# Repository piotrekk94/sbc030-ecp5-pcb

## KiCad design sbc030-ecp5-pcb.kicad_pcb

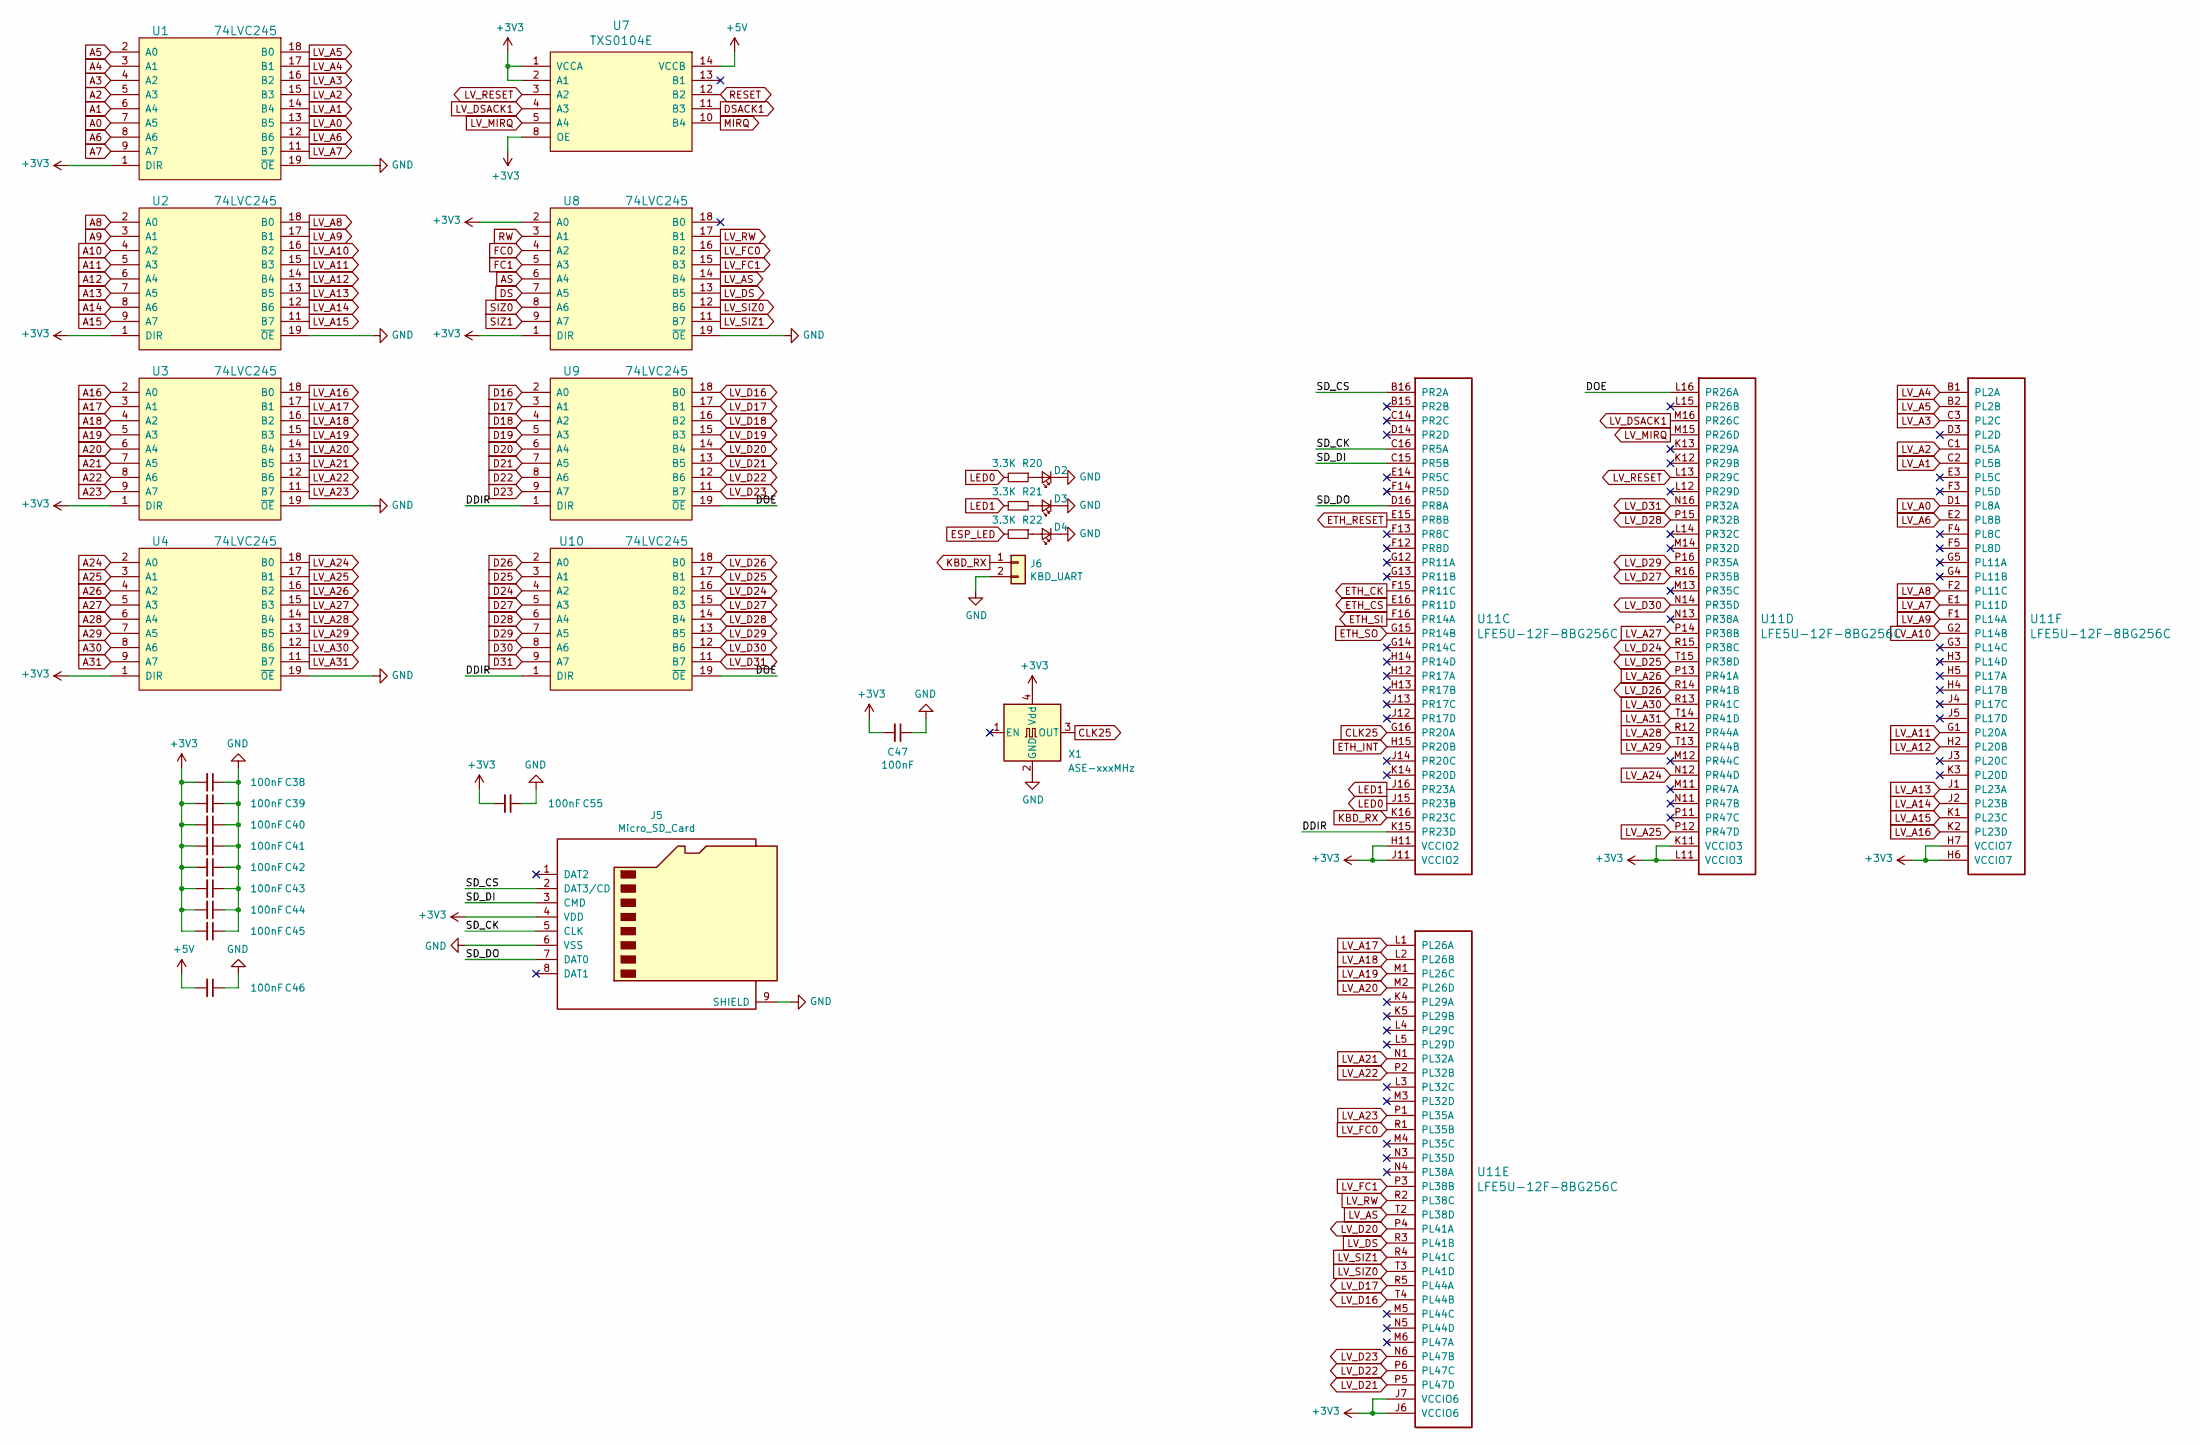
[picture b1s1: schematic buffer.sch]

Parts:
C38, C39, C40, C41, C42, C43, C44, C45, C46, C47, C55: 100nF; C_0603_1608Metric
D2, D3, D4: LED_Small; LED_0603_1608Metric
J5: Micro_SD_Card; microSD_HC_Wuerth_693072010801
J6: KBD_UART; PinHeader_1x02_P2.54mm_Vertical
R20, R21, R22: 3.3K; R_0603_1608Metric
U1, U2, U3, U4, U8, U9, U10: 74LVC245; TSSOP-20_4.4x6.5mm_P0.65mm
U7: TXS0104E; TSSOP-14_4.4x5mm_P0.65mm
U11: LFE5U-12F-8BG256C; BGA-256_14.0x14.0mm_Layout16x16_P0.8mm_Ball0.45mm_Pad0.32mm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
X1: ASE-xxxMHz; Oscillator_SMD_Abracon_ASE-4Pin_3.2x2.5mm

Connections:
+3V3: C38.2, C39.2, C40.2, C41.2, C42.2, C43.2, C44.2, C45.2, C47.2, C55.2, J5.4 (VDD), U1.1 (DIR), U1.20 (VCC), U2.1 (DIR), U2.20 (VCC), U3.1 (DIR), U3.20 (VCC), U4.1 (DIR), U4.20 (VCC), U7.1 (VCCA), U7.2 (A1), U7.8 (OE), U8.1 (DIR), U8.2 (A0), U8.20 (VCC), U9.20 (VCC), U10.20 (VCC), U11.H6 (VCCIO7), U11.H7 (VCCIO7), U11.H11 (VCCIO2), U11.J6 (VCCIO6), U11.J7 (VCCIO6), U11.J11 (VCCIO2), U11.K11 (VCCIO3), U11.L11 (VCCIO3), X1.4 (Vdd); also elsewhere on the board
+5V: C46.2, U7.14 (VCCB); also elsewhere on the board
/IO Buffers/DDIR: U9.1 (DIR), U10.1 (DIR), U11.K15 (PR23D)
/IO Buffers/DOE: U9.19 (~OE), U10.19 (~OE), U11.L16 (PR26A)
/IO Buffers/SD_CK: J5.5 (CLK), U11.C16 (PR5A)
/IO Buffers/SD_CS: J5.2 (DAT3/CD), U11.B16 (PR2A)
/IO Buffers/SD_DI: J5.3 (CMD), U11.C15 (PR5B)
/IO Buffers/SD_DO: J5.7 (DAT0), U11.D16 (PR8A)
A0: U1.7 (A5); also elsewhere on the board
A1: U1.6 (A4); also elsewhere on the board
A2: U1.5 (A3); also elsewhere on the board
A3: U1.4 (A2); also elsewhere on the board
A4: U1.3 (A1); also elsewhere on the board
A5: U1.2 (A0); also elsewhere on the board
A6: U1.8 (A6); also elsewhere on the board
A7: U1.9 (A7); also elsewhere on the board
A8: U2.2 (A0); also elsewhere on the board
A9: U2.3 (A1); also elsewhere on the board
A10: U2.4 (A2); also elsewhere on the board
A11: U2.5 (A3); also elsewhere on the board
A12: U2.6 (A4); also elsewhere on the board
A13: U2.7 (A5); also elsewhere on the board
A14: U2.8 (A6); also elsewhere on the board
A15: U2.9 (A7); also elsewhere on the board
A16: U3.2 (A0); also elsewhere on the board
A17: U3.3 (A1); also elsewhere on the board
A18: U3.4 (A2); also elsewhere on the board
A19: U3.5 (A3); also elsewhere on the board
A20: U3.6 (A4); also elsewhere on the board
A21: U3.7 (A5); also elsewhere on the board
A22: U3.8 (A6); also elsewhere on the board
A23: U3.9 (A7); also elsewhere on the board
A24: U4.2 (A0); also elsewhere on the board
A25: U4.3 (A1); also elsewhere on the board
A26: U4.4 (A2); also elsewhere on the board
A27: U4.5 (A3); also elsewhere on the board
A28: U4.6 (A4); also elsewhere on the board
A29: U4.7 (A5); also elsewhere on the board
A30: U4.8 (A6); also elsewhere on the board
A31: U4.9 (A7); also elsewhere on the board
AS: U8.6 (A4); also elsewhere on the board
CLK25: U11.G16 (PR20A), X1.3 (OUT); also elsewhere on the board
D16: U9.2 (A0); also elsewhere on the board
D17: U9.3 (A1); also elsewhere on the board
D18: U9.4 (A2); also elsewhere on the board
D19: U9.5 (A3); also elsewhere on the board
D20: U9.6 (A4); also elsewhere on the board
D21: U9.7 (A5); also elsewhere on the board
D22: U9.8 (A6); also elsewhere on the board
D23: U9.9 (A7); also elsewhere on the board
D24: U10.4 (A2); also elsewhere on the board
D25: U10.3 (A1); also elsewhere on the board
D26: U10.2 (A0); also elsewhere on the board
D27: U10.5 (A3); also elsewhere on the board
D28: U10.6 (A4); also elsewhere on the board
D29: U10.7 (A5); also elsewhere on the board
D30: U10.8 (A6); also elsewhere on the board
D31: U10.9 (A7); also elsewhere on the board
DS: U8.7 (A5); also elsewhere on the board
DSACK1: U7.11 (B3); also elsewhere on the board
ESP_LED: R22.2; also elsewhere on the board
ETH_CK: U11.F15 (PR11C); also elsewhere on the board
ETH_CS: U11.E16 (PR11D); also elsewhere on the board
ETH_INT: U11.H15 (PR20B); also elsewhere on the board
ETH_RESET: U11.E15 (PR8B); also elsewhere on the board
ETH_SI: U11.F16 (PR14A); also elsewhere on the board
ETH_SO: U11.G15 (PR14B); also elsewhere on the board
FC0: U8.4 (A2); also elsewhere on the board
FC1: U8.5 (A3); also elsewhere on the board
GND: C38.1, C39.1, C40.1, C41.1, C42.1, C43.1, C44.1, C45.1, C46.1, C47.1, C55.1, D2.1 (K), D3.1 (K), D4.1 (K), J5.6 (VSS), J5.9 (SHIELD), J6.2, U1.10 (GND), U1.19 (~OE), U2.10 (GND), U2.19 (~OE), U3.10 (GND), U3.19 (~OE), U4.10 (GND), U4.19 (~OE), U7.7 (GND), U8.10 (GND), U8.19 (~OE), U9.10 (GND), U10.10 (GND), X1.2 (GND); also elsewhere on the board
KBD_RX: J6.1, U11.K16 (PR23C)
LED0: R20.2, U11.J15 (PR23B)
LED1: R21.2, U11.J16 (PR23A)
LV_A0: U1.13 (B5), U11.D1 (PL8A)
LV_A1: U1.14 (B4), U11.C2 (PL5B)
LV_A2: U1.15 (B3), U11.C1 (PL5A)
LV_A3: U1.16 (B2), U11.C3 (PL2C)
LV_A4: U1.17 (B1), U11.B1 (PL2A)
LV_A5: U1.18 (B0), U11.B2 (PL2B)
LV_A6: U1.12 (B6), U11.E2 (PL8B)
LV_A7: U1.11 (B7), U11.E1 (PL11D)
LV_A8: U2.18 (B0), U11.F2 (PL11C)
LV_A9: U2.17 (B1), U11.F1 (PL14A)
LV_A10: U2.16 (B2), U11.G2 (PL14B)
LV_A11: U2.15 (B3), U11.G1 (PL20A)
LV_A12: U2.14 (B4), U11.H2 (PL20B)
LV_A13: U2.13 (B5), U11.J1 (PL23A)
LV_A14: U2.12 (B6), U11.J2 (PL23B)
LV_A15: U2.11 (B7), U11.K1 (PL23C)
LV_A16: U3.18 (B0), U11.K2 (PL23D)
LV_A17: U3.17 (B1), U11.L1 (PL26A)
LV_A18: U3.16 (B2), U11.L2 (PL26B)
LV_A19: U3.15 (B3), U11.M1 (PL26C)
LV_A20: U3.14 (B4), U11.M2 (PL26D)
LV_A21: U3.13 (B5), U11.N1 (PL32A)
LV_A22: U3.12 (B6), U11.P2 (PL32B)
LV_A23: U3.11 (B7), U11.P1 (PL35A)
LV_A24: U4.18 (B0), U11.N12 (PR44D)
LV_A25: U4.17 (B1), U11.P12 (PR47D)
LV_A26: U4.16 (B2), U11.P13 (PR41A)
LV_A27: U4.15 (B3), U11.P14 (PR38B)
LV_A28: U4.14 (B4), U11.R12 (PR44A)
LV_A29: U4.13 (B5), U11.T13 (PR44B)
LV_A30: U4.12 (B6), U11.R13 (PR41C)
LV_A31: U4.11 (B7), U11.T14 (PR41D)
LV_AS: U8.14 (B4), U11.T2 (PL38D)
LV_D16: U9.18 (B0), U11.T4 (PL44B)
LV_D17: U9.17 (B1), U11.R5 (PL44A)
LV_D18: U9.16 (B2); also elsewhere on the board
LV_D19: U9.15 (B3); also elsewhere on the board
LV_D20: U9.14 (B4), U11.P4 (PL41A)
LV_D21: U9.13 (B5), U11.P5 (PL47D)
LV_D22: U9.12 (B6), U11.P6 (PL47C)
LV_D23: U9.11 (B7), U11.N6 (PL47B)
LV_D24: U10.16 (B2), U11.R15 (PR38C)
LV_D25: U10.17 (B1), U11.T15 (PR38D)
LV_D26: U10.18 (B0), U11.R14 (PR41B)
LV_D27: U10.15 (B3), U11.R16 (PR35B)
LV_D28: U10.14 (B4), U11.P15 (PR32B)
LV_D29: U10.13 (B5), U11.P16 (PR35A)
LV_D30: U10.12 (B6), U11.N14 (PR35D)
LV_D31: U10.11 (B7), U11.N16 (PR32A)
LV_DS: U8.13 (B5), U11.R3 (PL41B)
LV_DSACK1: U7.4 (A3), U11.M16 (PR26C)
LV_FC0: U8.16 (B2), U11.R1 (PL35B)
LV_FC1: U8.15 (B3), U11.P3 (PL38B)
LV_MIRQ: U7.5 (A4), U11.M15 (PR26D)
LV_RESET: U7.3 (A2), U11.L13 (PR29C)
LV_RW: U8.17 (B1), U11.R2 (PL38C)
LV_SIZ0: U8.12 (B6), U11.T3 (PL41D)
LV_SIZ1: U8.11 (B7), U11.R4 (PL41C)
MIRQ: U7.10 (B4); also elsewhere on the board
unnamed: D2.2 (A), R20.1
unnamed: D3.2 (A), R21.1
unnamed: D4.2 (A), R22.1
RESET: U7.12 (B2); also elsewhere on the board
RW: U8.3 (A1); also elsewhere on the board
SIZ0: U8.8 (A6); also elsewhere on the board
SIZ1: U8.9 (A7); also elsewhere on the board

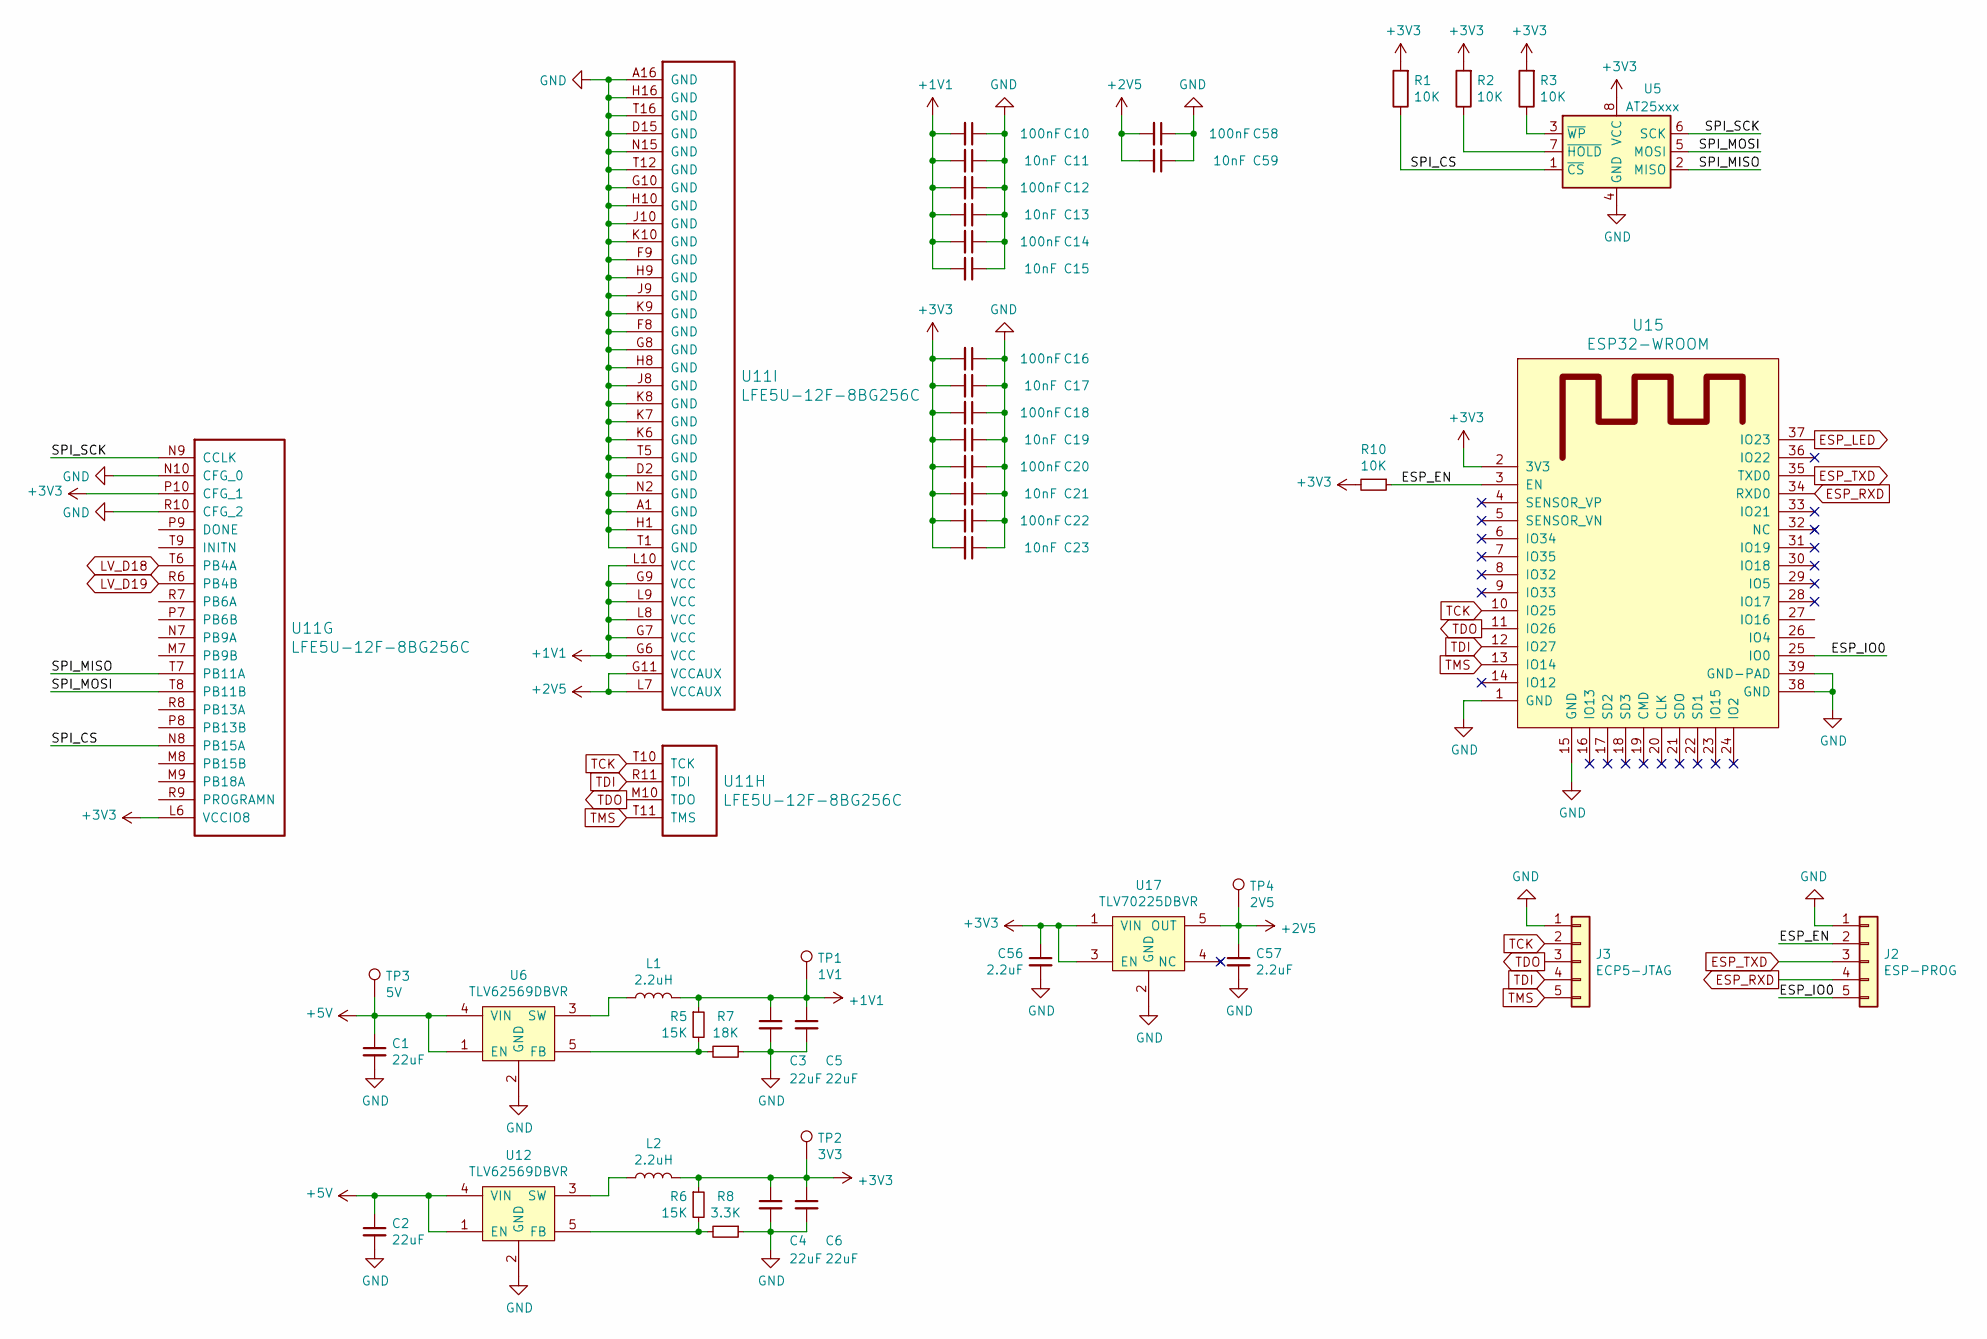
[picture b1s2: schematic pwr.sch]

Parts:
C1, C2, C3, C4, C5, C6: 22uF; C_0805_2012Metric
C10, C12, C14, C16, C18, C20, C22, C58: 100nF; C_0603_1608Metric
C11, C13, C15, C17, C19, C21, C23, C59: 10nF; C_0603_1608Metric
C56, C57: 2.2uF; C_0805_2012Metric
J2: ESP-PROG; PinHeader_1x05_P2.54mm_Vertical
J3: ECP5-JTAG; PinHeader_1x05_P2.54mm_Vertical
L1, L2: 2.2uH; L_1210_3225Metric
R1, R2, R3, R10: 10K; R_0603_1608Metric
R5, R6: 15K; R_0603_1608Metric
R7: 18K; R_0603_1608Metric
R8: 3.3K; R_0603_1608Metric
TP1: 1V1; TestPoint_Loop_D2.50mm_Drill1.0mm_LowProfile
TP2: 3V3; TestPoint_Loop_D2.50mm_Drill1.0mm_LowProfile
TP3: 5V; TestPoint_Loop_D2.50mm_Drill1.0mm_LowProfile
TP4: 2V5; TestPoint_Loop_D2.50mm_Drill1.0mm_LowProfile
U5: AT25xxx; SOIC-8_3.9x4.9mm_P1.27mm
U6, U12: TLV62569DBVR; SOT-23-5
U11: LFE5U-12F-8BG256C; BGA-256_14.0x14.0mm_Layout16x16_P0.8mm_Ball0.45mm_Pad0.32mm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
U15: ESP32-WROOM
U17: TLV70225DBVR; SOT-23-5

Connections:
+1V1: C3.1, C5.1, C10.2, C11.2, C12.2, C13.2, C14.2, C15.2, L1.2, R5.1, TP1.1, U11.G6 (VCC), U11.G7 (VCC), U11.G9 (VCC), U11.L8 (VCC), U11.L9 (VCC), U11.L10 (VCC)
+2V5: C57.1, C58.2, C59.2, TP4.1, U11.G11 (VCCAUX), U11.L7 (VCCAUX), U17.5 (OUT)
+3V3: C4.1, C6.1, C16.2, C17.2, C18.2, C19.2, C20.2, C21.2, C22.2, C23.2, C56.1, L2.2, R1.2, R2.2, R3.2, R6.1, R10.2, TP2.1, U5.8 (VCC), U11.L6 (VCCIO8), U11.P10 (CFG_1), U15.2 (3V3), U17.1 (VIN), U17.3 (EN); also elsewhere on the board
+5V: C1.1, C2.1, TP3.1, U6.1 (EN), U6.4 (VIN), U12.1 (EN), U12.4 (VIN); also elsewhere on the board
/Power & Flash/ESP_EN: J2.2, R10.1, U15.3 (EN)
/Power & Flash/ESP_IO0: J2.5, U15.25 (IO0)
/Power & Flash/SPI_CS: R1.1, U5.1 (~CS), U11.N8 (PB15A)
/Power & Flash/SPI_MISO: U5.2 (MISO), U11.T7 (PB11A)
/Power & Flash/SPI_MOSI: U5.5 (MOSI), U11.T8 (PB11B)
/Power & Flash/SPI_SCK: U5.6 (SCK), U11.N9 (CCLK)
ESP_LED: U15.37 (IO23); also elsewhere on the board
ESP_RXD: J2.4, U15.34 (RXD0); also elsewhere on the board
ESP_TXD: J2.3, U15.35 (TXD0); also elsewhere on the board
GND: C1.2, C2.2, C3.2, C4.2, C5.2, C6.2, C10.1, C11.1, C12.1, C13.1, C14.1, C15.1, C16.1, C17.1, C18.1, C19.1, C20.1, C21.1, C22.1, C23.1, C56.2, C57.2, C58.1, C59.1, J2.1, J3.1, R7.1, R8.1, U5.4 (GND), U6.2 (GND), U11.A1 (GND), U11.A16 (GND), U11.D2 (GND), U11.D15 (GND), U11.F8 (GND), U11.F9 (GND), U11.G8 (GND), U11.G10 (GND), U11.H1 (GND), U11.H8 (GND), U11.H9 (GND), U11.H10 (GND), U11.H16 (GND), U11.J8 (GND), U11.J9 (GND), U11.J10 (GND), U11.K6 (GND), U11.K7 (GND), U11.K8 (GND), U11.K9 (GND), U11.K10 (GND), U11.N2 (GND), U11.N10 (CFG_0), U11.N15 (GND), U11.R10 (CFG_2), U11.T1 (GND), U11.T5 (GND), U11.T12 (GND), U11.T16 (GND), U12.2 (GND), U15.1 (GND), U15.15 (GND), U15.38 (GND), U15.39 (GND-PAD), U17.2 (GND); also elsewhere on the board
LV_D18: U11.T6 (PB4A); also elsewhere on the board
LV_D19: U11.R6 (PB4B); also elsewhere on the board
unnamed: L1.1, U6.3 (SW)
unnamed: L2.1, U12.3 (SW)
unnamed: R2.1, U5.7 (~HOLD)
unnamed: R3.1, U5.3 (~WP)
unnamed: R5.2, R7.2, U6.5 (FB)
unnamed: R6.2, R8.2, U12.5 (FB)
TCK: J3.2, U11.T10 (TCK), U15.10 (IO25)
TDI: J3.4, U11.R11 (TDI), U15.12 (IO27)
TDO: J3.3, U11.M10 (TDO), U15.11 (IO26)
TMS: J3.5, U11.T11 (TMS), U15.13 (IO14)

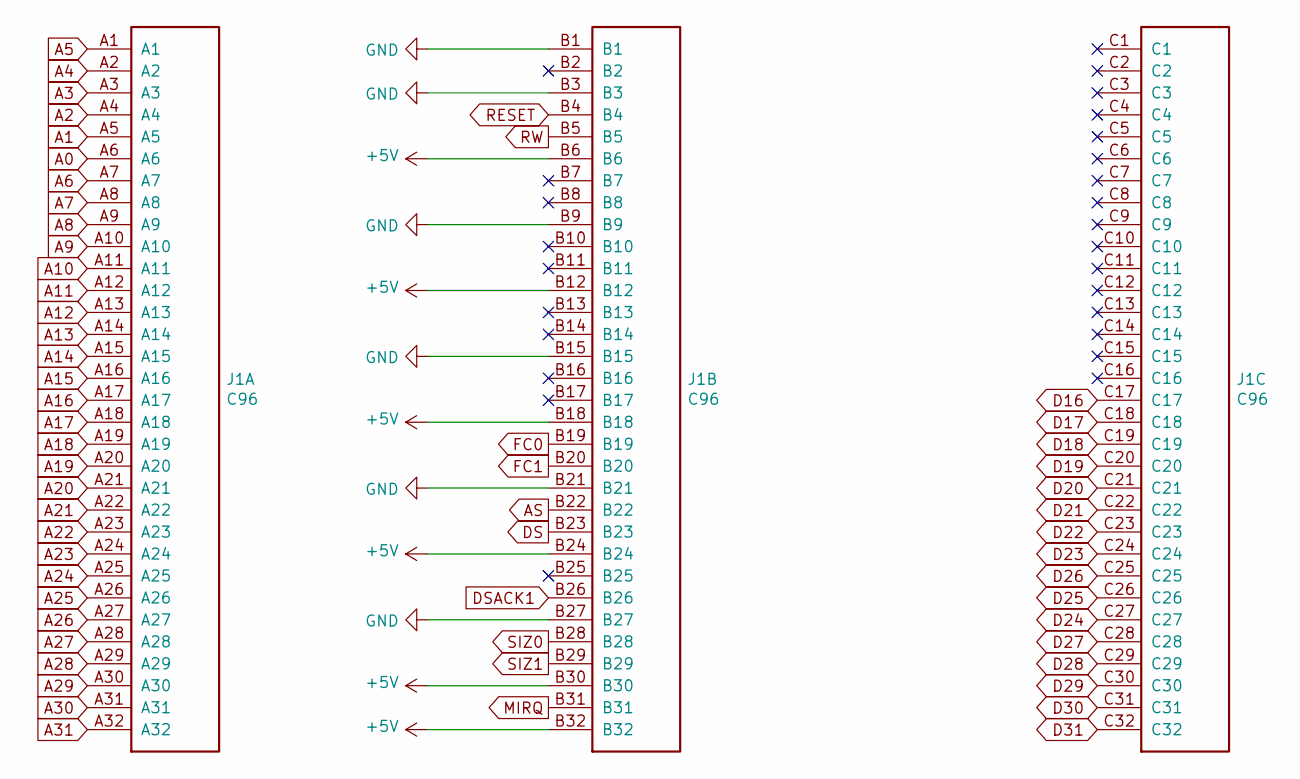
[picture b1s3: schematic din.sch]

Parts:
J1: C96; C96ABCM

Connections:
+5V: J1.B6, J1.B12, J1.B18, J1.B24, J1.B30, J1.B32; also elsewhere on the board
A0: J1.A6; also elsewhere on the board
A1: J1.A5; also elsewhere on the board
A2: J1.A4; also elsewhere on the board
A3: J1.A3; also elsewhere on the board
A4: J1.A2; also elsewhere on the board
A5: J1.A1; also elsewhere on the board
A6: J1.A7; also elsewhere on the board
A7: J1.A8; also elsewhere on the board
A8: J1.A9; also elsewhere on the board
A9: J1.A10; also elsewhere on the board
A10: J1.A11; also elsewhere on the board
A11: J1.A12; also elsewhere on the board
A12: J1.A13; also elsewhere on the board
A13: J1.A14; also elsewhere on the board
A14: J1.A15; also elsewhere on the board
A15: J1.A16; also elsewhere on the board
A16: J1.A17; also elsewhere on the board
A17: J1.A18; also elsewhere on the board
A18: J1.A19; also elsewhere on the board
A19: J1.A20; also elsewhere on the board
A20: J1.A21; also elsewhere on the board
A21: J1.A22; also elsewhere on the board
A22: J1.A23; also elsewhere on the board
A23: J1.A24; also elsewhere on the board
A24: J1.A25; also elsewhere on the board
A25: J1.A26; also elsewhere on the board
A26: J1.A27; also elsewhere on the board
A27: J1.A28; also elsewhere on the board
A28: J1.A29; also elsewhere on the board
A29: J1.A30; also elsewhere on the board
A30: J1.A31; also elsewhere on the board
A31: J1.A32; also elsewhere on the board
AS: J1.B22; also elsewhere on the board
D16: J1.C17; also elsewhere on the board
D17: J1.C18; also elsewhere on the board
D18: J1.C19; also elsewhere on the board
D19: J1.C20; also elsewhere on the board
D20: J1.C21; also elsewhere on the board
D21: J1.C22; also elsewhere on the board
D22: J1.C23; also elsewhere on the board
D23: J1.C24; also elsewhere on the board
D24: J1.C27; also elsewhere on the board
D25: J1.C26; also elsewhere on the board
D26: J1.C25; also elsewhere on the board
D27: J1.C28; also elsewhere on the board
D28: J1.C29; also elsewhere on the board
D29: J1.C30; also elsewhere on the board
D30: J1.C31; also elsewhere on the board
D31: J1.C32; also elsewhere on the board
DS: J1.B23; also elsewhere on the board
DSACK1: J1.B26; also elsewhere on the board
FC0: J1.B19; also elsewhere on the board
FC1: J1.B20; also elsewhere on the board
GND: J1.B1, J1.B3, J1.B9, J1.B15, J1.B21, J1.B27; also elsewhere on the board
MIRQ: J1.B31; also elsewhere on the board
RESET: J1.B4; also elsewhere on the board
RW: J1.B5; also elsewhere on the board
SIZ0: J1.B28; also elsewhere on the board
SIZ1: J1.B29; also elsewhere on the board

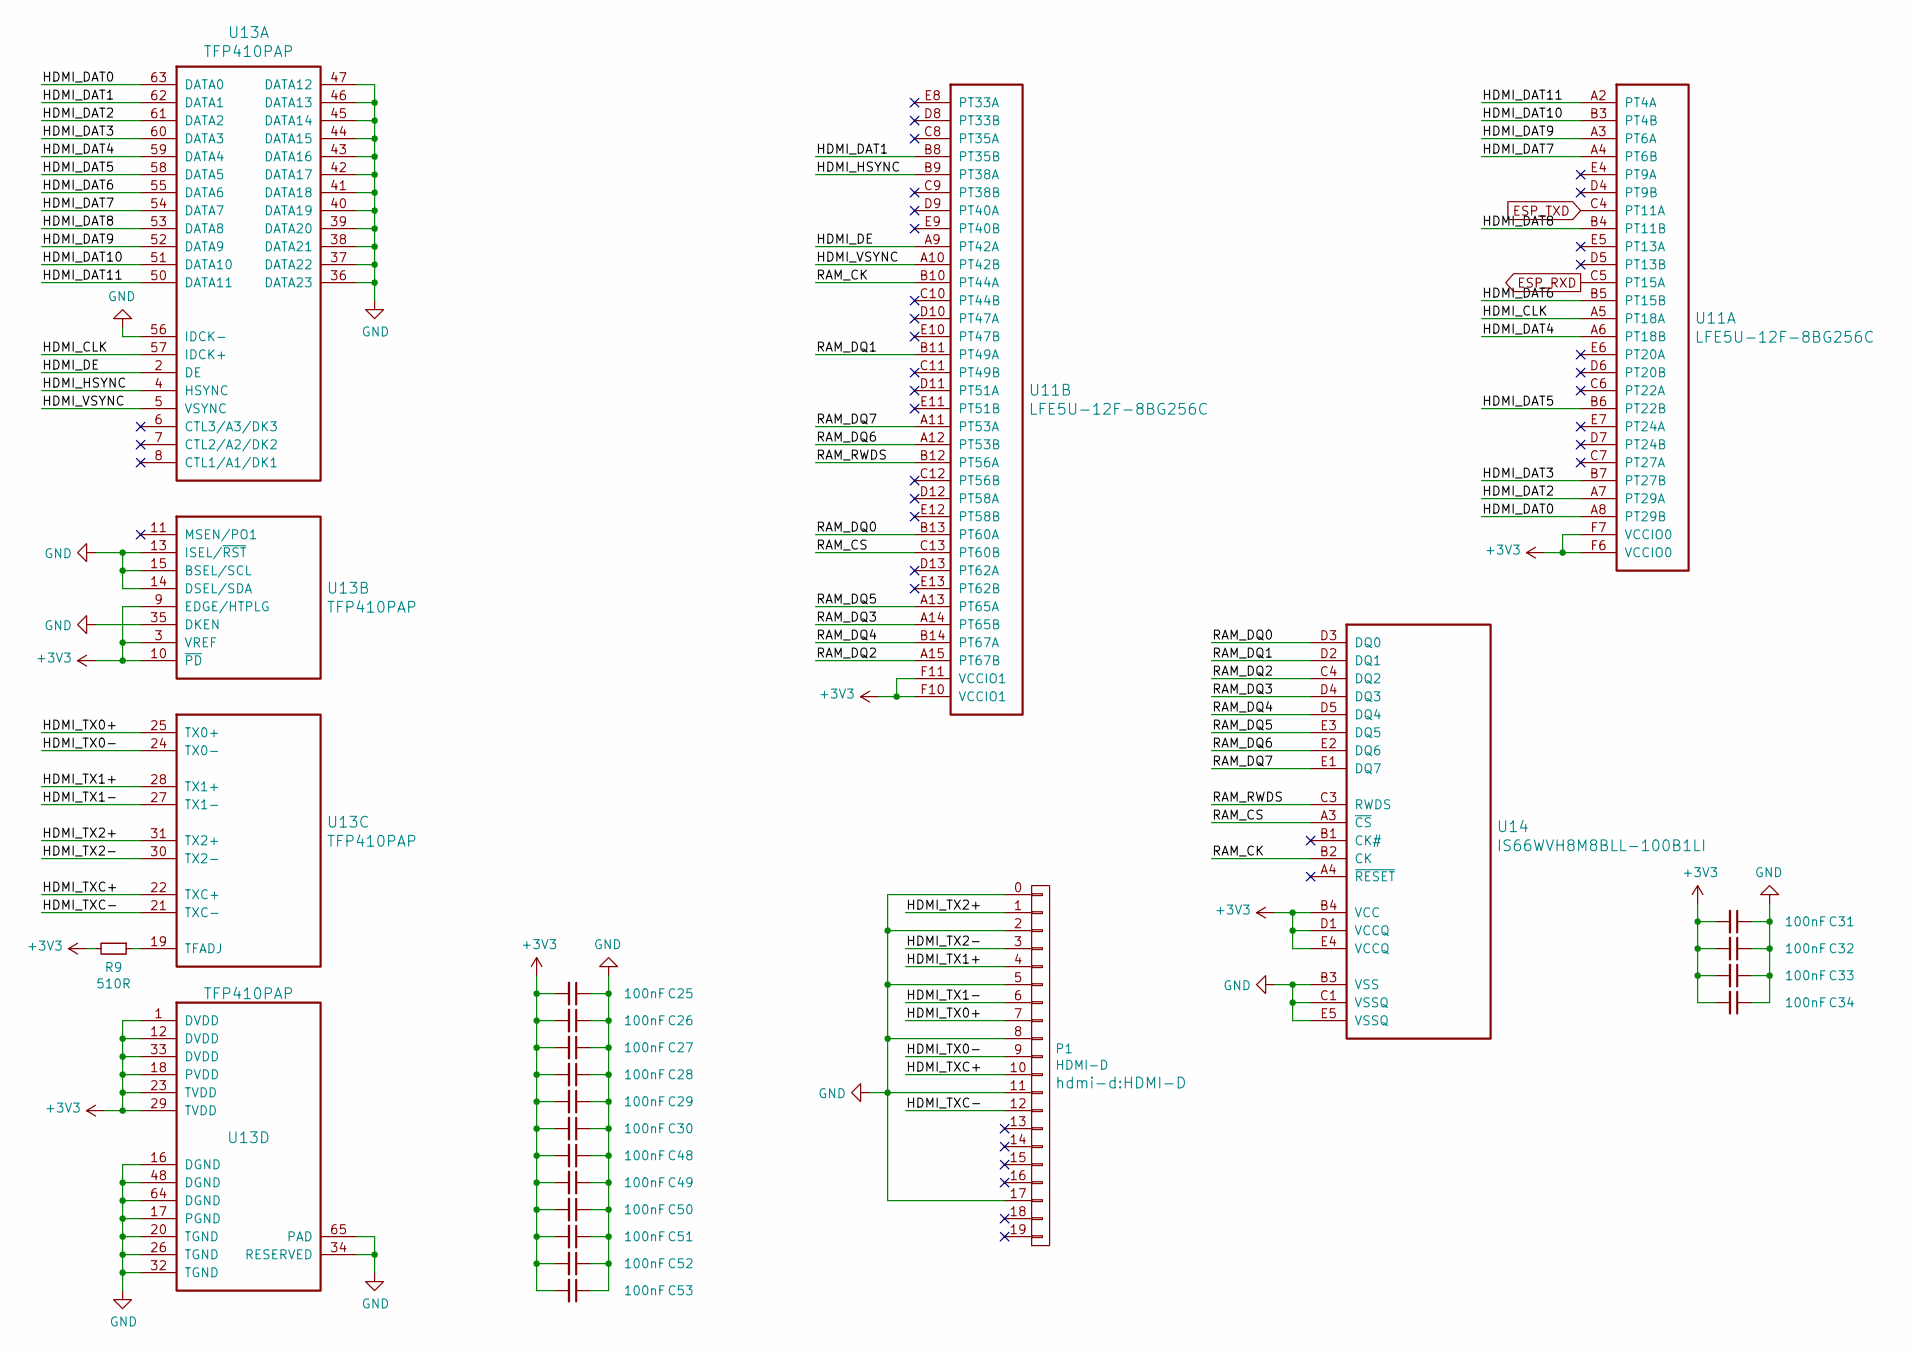
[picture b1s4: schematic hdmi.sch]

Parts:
C25, C26, C27, C28, C29, C30, C31, C32, C33, C34, C48, C49, C50, C51, C52, C53: 100nF; C_0603_1608Metric
P1: HDMI-D
R9: 510R; R_0603_1608Metric
U11: LFE5U-12F-8BG256C; BGA-256_14.0x14.0mm_Layout16x16_P0.8mm_Ball0.45mm_Pad0.32mm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
U13: TFP410PAP; LQFP-64-1EP_10x10mm_P0.5mm_EP6.5x6.5mm
U14: IS66WVH8M8BLL-100B1LI; TFBGA25

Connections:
+3V3: C25.2, C26.2, C27.2, C28.2, C29.2, C30.2, C31.2, C32.2, C33.2, C34.2, C48.2, C49.2, C50.2, C51.2, C52.2, C53.2, R9.2, U11.F6 (VCCIO0), U11.F7 (VCCIO0), U11.F10 (VCCIO1), U11.F11 (VCCIO1), U13.1 (DVDD), U13.3 (VREF), U13.9 (EDGE/HTPLG), U13.10 (~PD), U13.12 (DVDD), U13.18 (PVDD), U13.23 (TVDD), U13.29 (TVDD), U13.33 (DVDD), U14.B4 (VCC), U14.D1 (VCCQ), U14.E4 (VCCQ); also elsewhere on the board
/HDMI/HDMI_CLK: U11.A5 (PT18A), U13.57 (IDCK+)
/HDMI/HDMI_DAT0: U11.A8 (PT29B), U13.63 (DATA0)
/HDMI/HDMI_DAT1: U11.B8 (PT35B), U13.62 (DATA1)
/HDMI/HDMI_DAT2: U11.A7 (PT29A), U13.61 (DATA2)
/HDMI/HDMI_DAT3: U11.B7 (PT27B), U13.60 (DATA3)
/HDMI/HDMI_DAT4: U11.A6 (PT18B), U13.59 (DATA4)
/HDMI/HDMI_DAT5: U11.B6 (PT22B), U13.58 (DATA5)
/HDMI/HDMI_DAT6: U11.B5 (PT15B), U13.55 (DATA6)
/HDMI/HDMI_DAT7: U11.A4 (PT6B), U13.54 (DATA7)
/HDMI/HDMI_DAT8: U11.B4 (PT11B), U13.53 (DATA8)
/HDMI/HDMI_DAT9: U11.A3 (PT6A), U13.52 (DATA9)
/HDMI/HDMI_DAT10: U11.B3 (PT4B), U13.51 (DATA10)
/HDMI/HDMI_DAT11: U11.A2 (PT4A), U13.50 (DATA11)
/HDMI/HDMI_DE: U11.A9 (PT42A), U13.2 (DE)
/HDMI/HDMI_HSYNC: U11.B9 (PT38A), U13.4 (HSYNC)
/HDMI/HDMI_TX0+: P1.7, U13.25 (TX0+)
/HDMI/HDMI_TX0-: P1.9, U13.24 (TX0-)
/HDMI/HDMI_TX1+: P1.4, U13.28 (TX1+)
/HDMI/HDMI_TX1-: P1.6, U13.27 (TX1-)
/HDMI/HDMI_TX2+: P1.1, U13.31 (TX2+)
/HDMI/HDMI_TX2-: P1.3, U13.30 (TX2-)
/HDMI/HDMI_TXC+: P1.10, U13.22 (TXC+)
/HDMI/HDMI_TXC-: P1.12, U13.21 (TXC-)
/HDMI/HDMI_VSYNC: U11.A10 (PT42B), U13.5 (VSYNC)
/HDMI/RAM_CK: U11.B10 (PT44A), U14.B2 (CK)
/HDMI/RAM_CS: U11.C13 (PT60B), U14.A3 (~CS)
/HDMI/RAM_DQ0: U11.B13 (PT60A), U14.D3 (DQ0)
/HDMI/RAM_DQ1: U11.B11 (PT49A), U14.D2 (DQ1)
/HDMI/RAM_DQ2: U11.A15 (PT67B), U14.C4 (DQ2)
/HDMI/RAM_DQ3: U11.A14 (PT65B), U14.D4 (DQ3)
/HDMI/RAM_DQ4: U11.B14 (PT67A), U14.D5 (DQ4)
/HDMI/RAM_DQ5: U11.A13 (PT65A), U14.E3 (DQ5)
/HDMI/RAM_DQ6: U11.A12 (PT53B), U14.E2 (DQ6)
/HDMI/RAM_DQ7: U11.A11 (PT53A), U14.E1 (DQ7)
/HDMI/RAM_RWDS: U11.B12 (PT56A), U14.C3 (RWDS)
ESP_RXD: U11.C5 (PT15A); also elsewhere on the board
ESP_TXD: U11.C4 (PT11A); also elsewhere on the board
GND: C25.1, C26.1, C27.1, C28.1, C29.1, C30.1, C31.1, C32.1, C33.1, C34.1, C48.1, C49.1, C50.1, C51.1, C52.1, C53.1, P1.0, P1.2, P1.5, P1.8, P1.11, P1.17, U13.13 (ISEL/~RST), U13.14 (DSEL/SDA), U13.15 (BSEL/SCL), U13.16 (DGND), U13.17 (PGND), U13.20 (TGND), U13.26 (TGND), U13.32 (TGND), U13.34 (RESERVED), U13.35 (DKEN), U13.36 (DATA23), U13.37 (DATA22), U13.38 (DATA21), U13.39 (DATA20), U13.40 (DATA19), U13.41 (DATA18), U13.42 (DATA17), U13.43 (DATA16), U13.44 (DATA15), U13.45 (DATA14), U13.46 (DATA13), U13.47 (DATA12), U13.48 (DGND), U13.56 (IDCK-), U13.64 (DGND), U13.65 (PAD), U14.B3 (VSS), U14.C1 (VSSQ), U14.E5 (VSSQ); also elsewhere on the board
unnamed: R9.1, U13.19 (TFADJ)

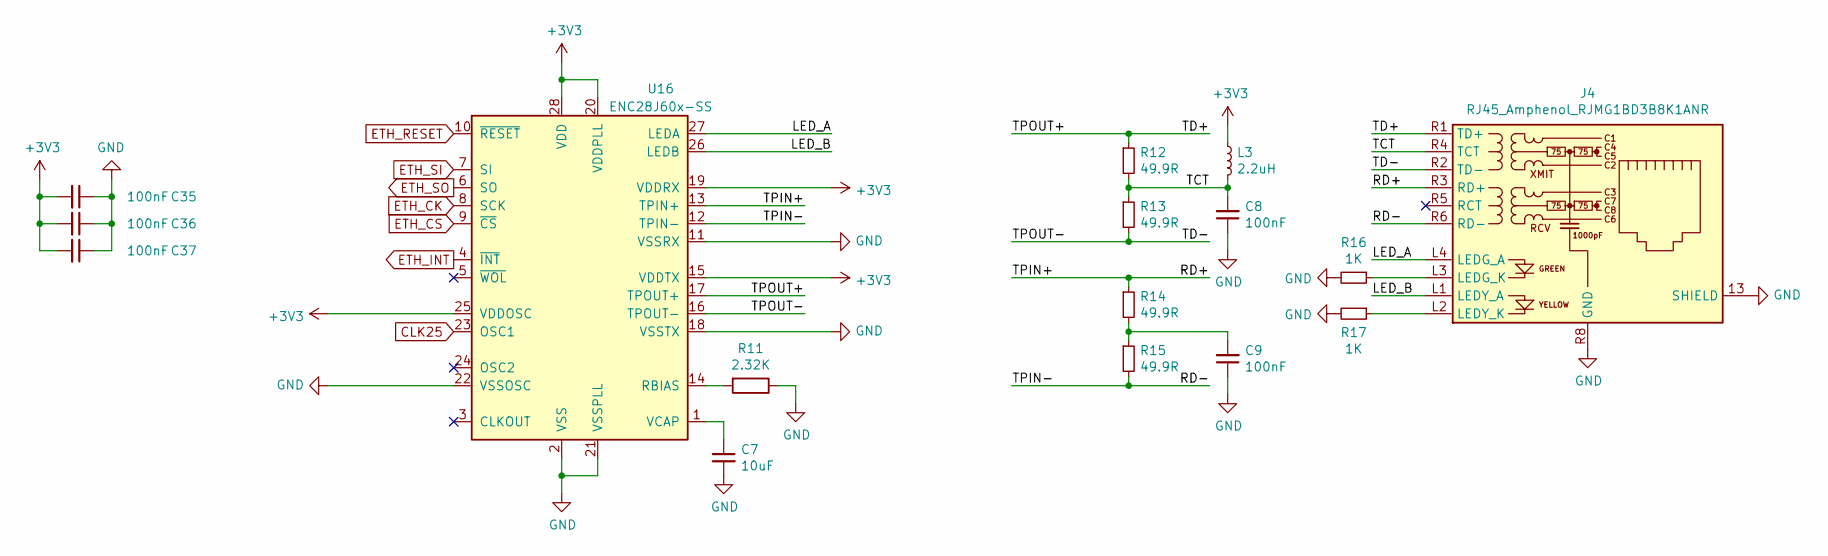
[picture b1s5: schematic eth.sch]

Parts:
C7: 10uF; C_0603_1608Metric
C8, C9, C35, C36, C37: 100nF; C_0603_1608Metric
J4: RJ45_Amphenol_RJMG1BD3B8K1ANR
L3: 2.2uH; L_1210_3225Metric
R11: 2.32K; R_0603_1608Metric
R12, R13, R14, R15: 49.9R; R_0603_1608Metric
R16, R17: 1K; R_0603_1608Metric
U16: ENC28J60x-SS; SSOP-28_5.3x10.2mm_P0.65mm

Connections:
+3V3: C35.2, C36.2, C37.2, L3.1, U16.15 (VDDTX), U16.19 (VDDRX), U16.20 (VDDPLL), U16.25 (VDDOSC), U16.28 (VDD); also elsewhere on the board
/Ethernet/LED_A: J4.L4 (LEDG_A), U16.27 (LEDA)
/Ethernet/LED_B: J4.L1 (LEDY_A), U16.26 (LEDB)
/Ethernet/RD+: J4.R3 (RD+), R14.1, U16.13 (TPIN+)
/Ethernet/RD-: J4.R6 (RD-), R15.2, U16.12 (TPIN-)
/Ethernet/TCT: C8.2, J4.R4 (TCT), L3.2, R12.2, R13.1
/Ethernet/TD+: J4.R1 (TD+), R12.1, U16.17 (TPOUT+)
/Ethernet/TD-: J4.R2 (TD-), R13.2, U16.16 (TPOUT-)
CLK25: U16.23 (OSC1); also elsewhere on the board
ETH_CK: U16.8 (SCK); also elsewhere on the board
ETH_CS: U16.9 (~CS); also elsewhere on the board
ETH_INT: U16.4 (~INT); also elsewhere on the board
ETH_RESET: U16.10 (~RESET); also elsewhere on the board
ETH_SI: U16.7 (SI); also elsewhere on the board
ETH_SO: U16.6 (SO); also elsewhere on the board
GND: C7.2, C8.1, C9.1, C35.1, C36.1, C37.1, J4.13 (SHIELD), J4.R8 (GND), R11.1, R16.2, R17.2, U16.2 (VSS), U16.11 (VSSRX), U16.18 (VSSTX), U16.21 (VSSPLL), U16.22 (VSSOSC); also elsewhere on the board
unnamed: C7.1, U16.1 (VCAP)
unnamed: C9.2, R14.2, R15.1
unnamed: J4.L2 (LEDY_K), R17.1
unnamed: J4.L3 (LEDG_K), R16.1
unnamed: R11.2, U16.14 (RBIAS)
